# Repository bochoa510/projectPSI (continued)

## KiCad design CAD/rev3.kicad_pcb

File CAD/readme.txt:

Created using OnShape 3D CAD and 3D printed test parts using Makerbot Replicator 5th Gen 

Link to part document
https://cad.onshape.com/documents/6e8889402c3ba4208828449b/w/36755877a1c921f2bab17a01/e/a95ed9e188de5fe185a65eca

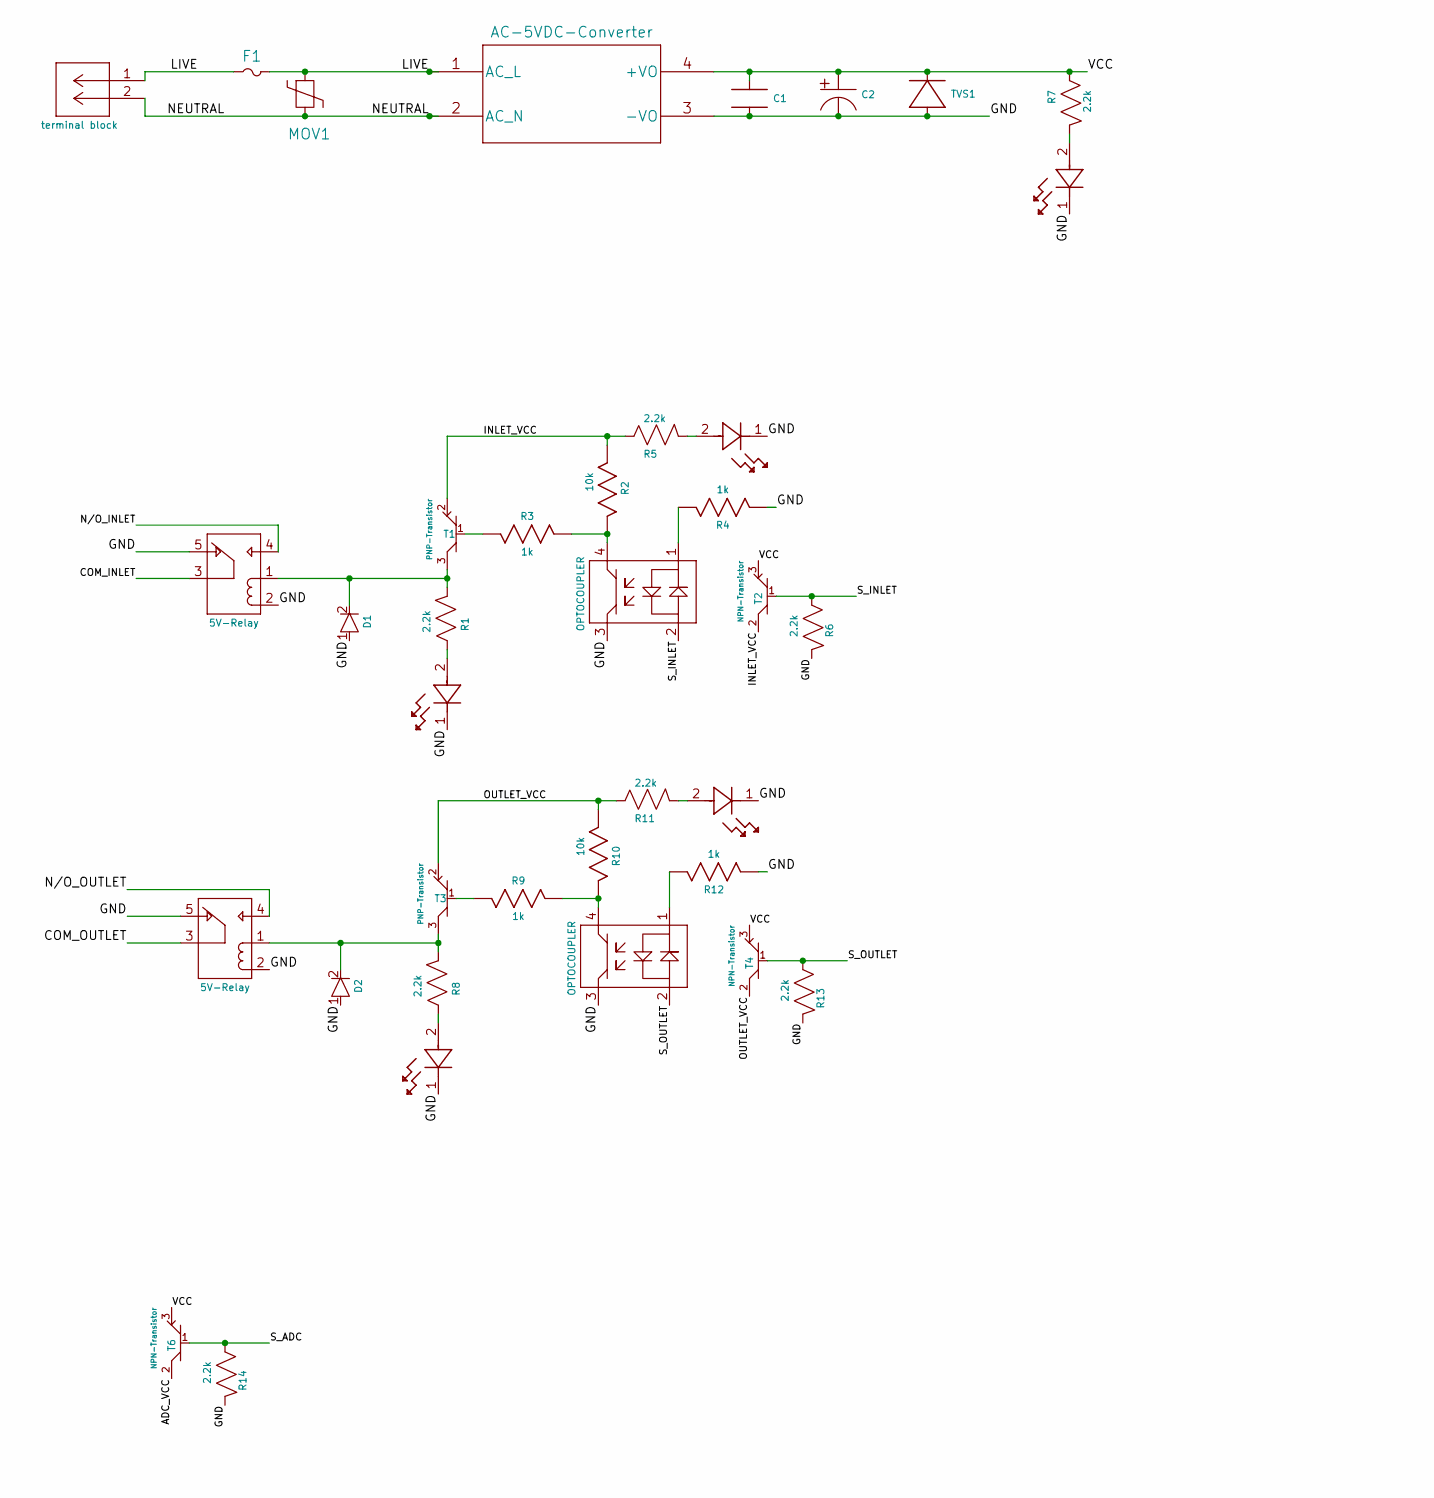
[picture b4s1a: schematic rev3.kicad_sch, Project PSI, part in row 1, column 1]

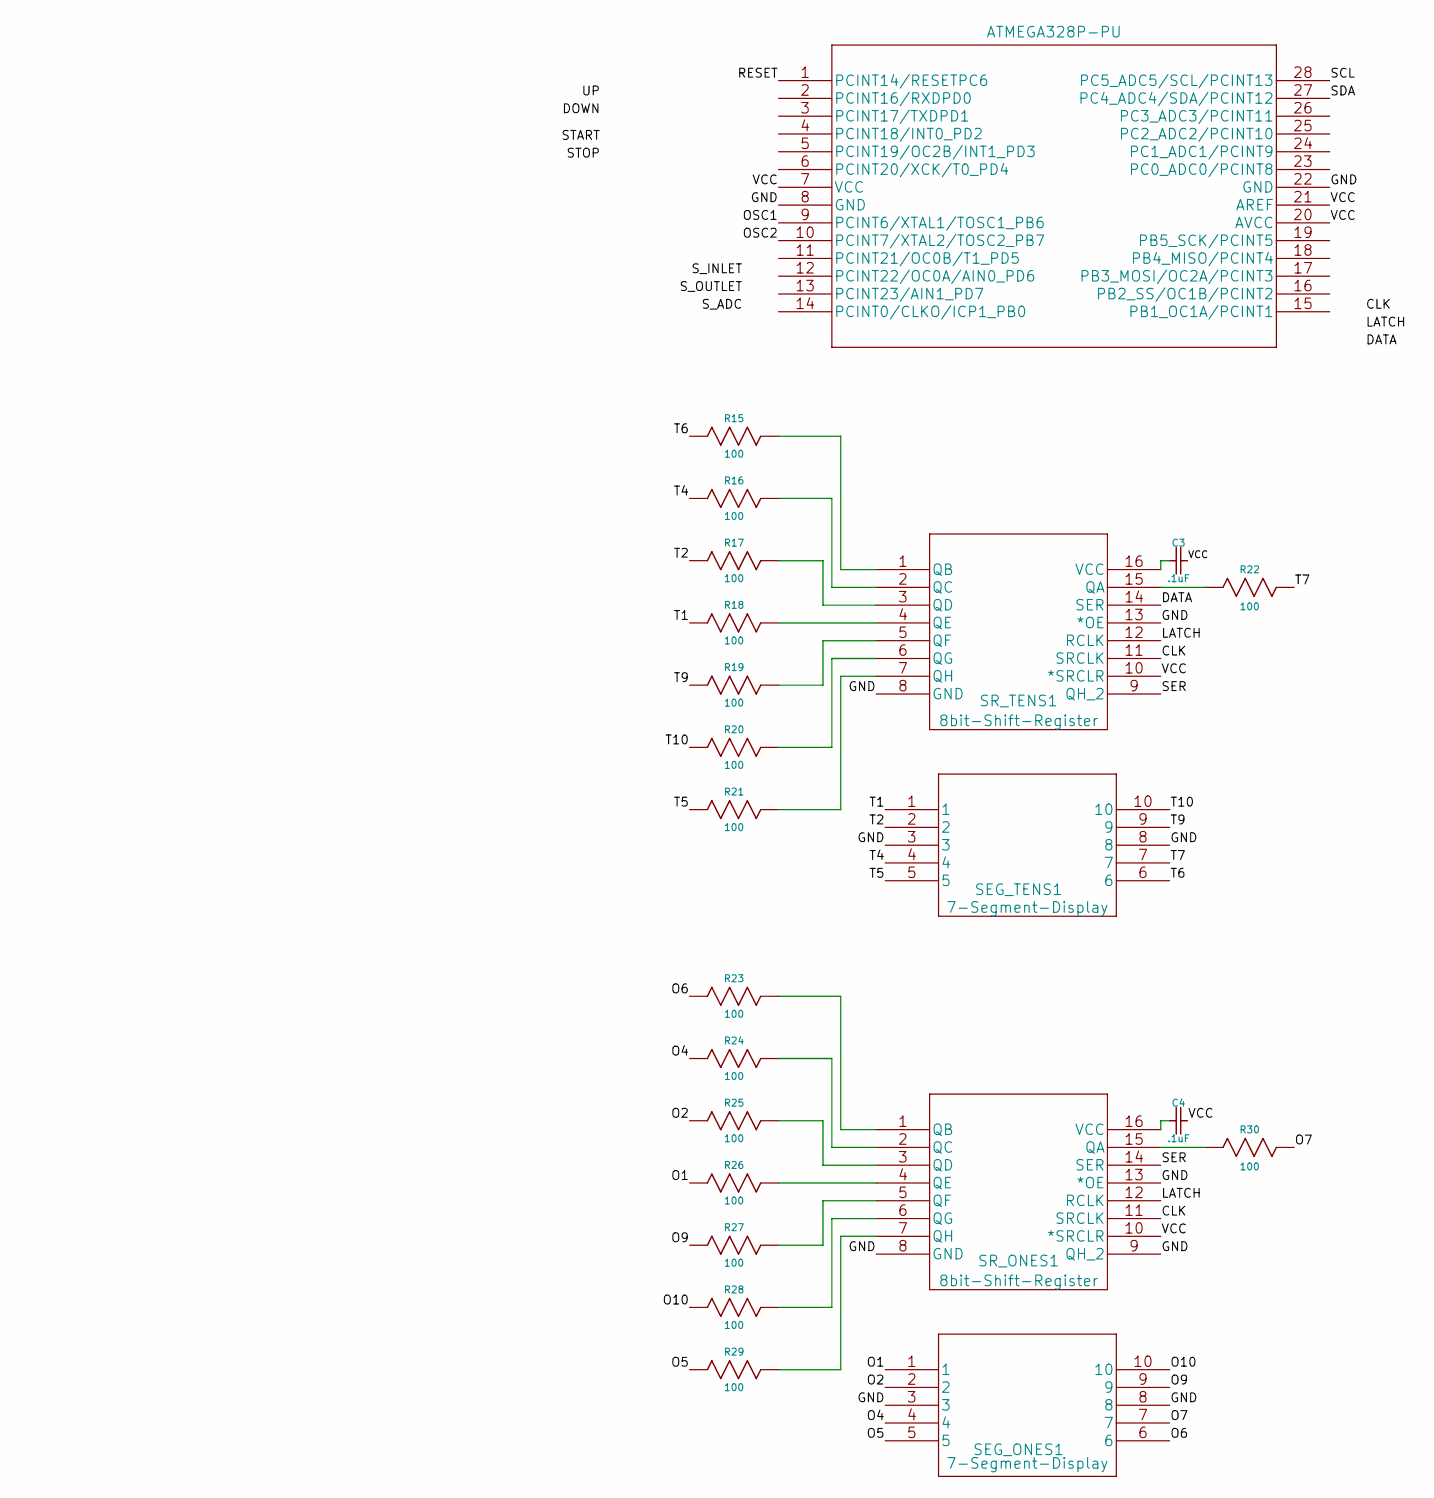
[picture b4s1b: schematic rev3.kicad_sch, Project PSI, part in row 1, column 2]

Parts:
C1: 1uF-Ceramic-Capacitor; 1uF ceramic capacitor
C2: 220uF-Electrolytic-Capacitor; 220uF electrolytic capacitor
C3, C4: .1uF; .1uF ceramic capacitor
D1, D2: Small-Signal-Diode; small signal diode
F1: FUSE
J1, J3: 5V-Relay; 5V Relay
J2: terminal block; 2-pin-terminal-block
LED1, LED3, LED5: green led; green LED
LED2, LED4: red led; red LED
MOV1: 470V-Varistor; 470V Varistor
Q1, Q2: OPTOCOUPLER; optocoupler
R1, R5, R6, R7, R8, R11, R13, R14: 2.2k; 2.2kohm resisitor
R2, R10: 10k; 10kohm resistor
R3, R4, R9, R12: 1k; 1kohm resistor
R15, R16, R17, R18, R19, R20, R21, R22, R23, R24, R25, R26, R27, R28, R29, R30: 100; 100ohm resistor
SEG_ONES1: 7-Segment-Display; 7 segment display
SEG_TENS1: 7-Segment-Display; 7 segment display
SR_ONES1: 8bit-Shift-Register; 8 bit shift register
SR_TENS1: 8bit-Shift-Register; 8 bit shift register
T1, T3: PNP-Transistor; PNP Transistor
T2, T4, T6: NPN-Transistor; NPN Transistor
TVS1: 7A-TVS-DIODE; 7A TVS diode
p1: ATMEGA328P-PU
u1: AC-5VDC-Converter; ac-dc converter

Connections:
/ADC_VCC: T6.2
/COM_INLET: J1.3
/COM_OUTLET: J3.3
/GND: C1.1, C2.2, D1.1, D2.1, J1.2, J1.5, J3.2, J3.5, LED1.1, LED2.1, LED3.1, LED4.1, LED5.1, Q1.3, Q2.3, R4.2, R6.1, R12.2, R13.1, R14.1, SEG_ONES1.3, SEG_ONES1.8, SEG_TENS1.3, SEG_TENS1.8, SR_ONES1.8 (GND), SR_ONES1.9 (QH_2), SR_ONES1.13 (*OE), SR_TENS1.8 (GND), SR_TENS1.13 (*OE), TVS1.2, p1.8 (GND), p1.22 (GND), u1.3 (-VO); also elsewhere on the board
/INLET_VCC: R2.2, R5.2, T1.2, T2.2
/LIVE: F1.1, F1.2, J2.1, MOV1.2, u1.1 (AC_L)
/NEUTRAL: J2.2, MOV1.1, u1.2 (AC_N)
/N/O_INLET: J1.4
/N/O_OUTLET: J3.4
/O1: R26.1, SEG_ONES1.1
/O2: R25.1, SEG_ONES1.2
/O4: R24.1, SEG_ONES1.4
/O5: R29.1, SEG_ONES1.5
/O6: R23.1, SEG_ONES1.6
/O7: R30.1, SEG_ONES1.7
/O9: R27.1, SEG_ONES1.9
/O10: R28.1, SEG_ONES1.10
/OSC1: p1.9 (PCINT6/XTAL1/TOSC1_PB6)
/OSC2: p1.10 (PCINT7/XTAL2/TOSC2_PB7)
/OUTLET_VCC: R10.2, R11.2, T3.2, T4.2
/RESET: p1.1 (PCINT14/RESETPC6)
/SCL: p1.28 (PC5_ADC5/SCL/PCINT13)
/SDA: p1.27 (PC4_ADC4/SDA/PCINT12)
/S_ADC: R14.2, T6.1
/S_INLET: Q1.2, R6.2, T2.1
/S_OUTLET: Q2.2, R13.2, T4.1
/T1: R18.1, SEG_TENS1.1
/T2: R17.1, SEG_TENS1.2
/T4: R16.1, SEG_TENS1.4
/T5: R21.1, SEG_TENS1.5
/T6: R15.1, SEG_TENS1.6
/T7: R22.1, SEG_TENS1.7
/T9: R19.1, SEG_TENS1.9
/T10: R20.1, SEG_TENS1.10
/VCC: C1.2, C2.1, C3.2, C4.2, R7.2, SR_ONES1.10 (*SRCLR), SR_TENS1.10 (*SRCLR), T2.3, T4.3, T6.3, TVS1.1, p1.7 (VCC), p1.20 (AVCC), p1.21 (AREF), u1.4 (+VO); also elsewhere on the board
unnamed: D1.2, J1.1, R1.1, T1.3
unnamed: D2.2, J3.1, R8.1, T3.3
unnamed: LED1.2, R5.1
unnamed: LED2.2, R1.2
unnamed: LED3.2, R7.1
unnamed: LED4.2, R8.2
unnamed: LED5.2, R11.1
unnamed: Q1.1, R4.1
unnamed: Q1.4, R2.1, R3.1
unnamed: Q2.1, R12.1
unnamed: Q2.4, R9.1, R10.1
unnamed: R3.2, T1.1
unnamed: R9.2, T3.1
unnamed: SR_ONES1.11 (SRCLK), SR_TENS1.11 (SRCLK)
unnamed: SR_ONES1.12 (RCLK), SR_TENS1.12 (RCLK)
unnamed: SR_ONES1.14 (SER), SR_TENS1.9 (QH_2)
unnamed 55: R30.2, SR_ONES1.15 (QA); also elsewhere on the board
unnamed 56: R23.2, SR_ONES1.1 (QB); also elsewhere on the board
unnamed 57: R24.2, SR_ONES1.2 (QC); also elsewhere on the board
unnamed 58: R25.2, SR_ONES1.3 (QD); also elsewhere on the board
unnamed 59: R26.2, SR_ONES1.4 (QE); also elsewhere on the board
unnamed 60: R27.2, SR_ONES1.5 (QF); also elsewhere on the board
unnamed 61: R28.2, SR_ONES1.6 (QG); also elsewhere on the board
unnamed 62: R29.2, SR_ONES1.7 (QH); also elsewhere on the board
unnamed 63: C4.1, SR_ONES1.16 (VCC); also elsewhere on the board
unnamed 64: R22.2, SR_TENS1.15 (QA); also elsewhere on the board
unnamed 65: R15.2, SR_TENS1.1 (QB); also elsewhere on the board
unnamed 66: R16.2, SR_TENS1.2 (QC); also elsewhere on the board
unnamed 67: R17.2, SR_TENS1.3 (QD); also elsewhere on the board
unnamed 68: R18.2, SR_TENS1.4 (QE); also elsewhere on the board
unnamed 69: R19.2, SR_TENS1.5 (QF); also elsewhere on the board
unnamed 70: R20.2, SR_TENS1.6 (QG); also elsewhere on the board
unnamed 71: R21.2, SR_TENS1.7 (QH); also elsewhere on the board
unnamed 72: C3.1, SR_TENS1.16 (VCC); also elsewhere on the board

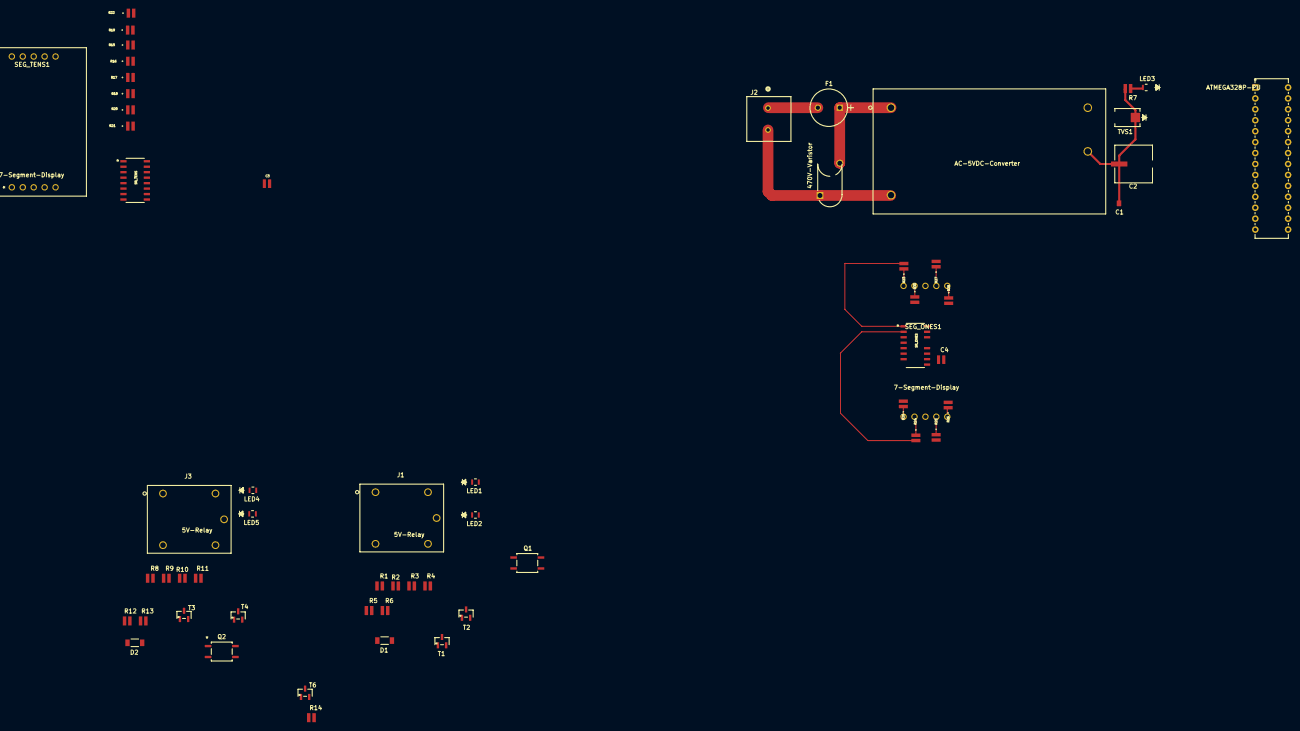
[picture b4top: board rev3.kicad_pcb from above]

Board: 2 copper layers, 60 parts (1 on the bottom side), 59 nets.

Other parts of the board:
SR_ONES: 8bit-Shift-Register; 8 bit shift register
SR_TENS: 8bit-Shift-Register; 8 bit shift register

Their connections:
/CLK: SR_ONES.11 (SRCLK), SR_TENS.11 (SRCLK)
/GND: SR_ONES.8 (GND), SR_ONES.9 (QH_2), SR_ONES.13 (*OE), SR_TENS.8 (GND), SR_TENS.13 (*OE); also elsewhere on the board
/LATCH: SR_ONES.12 (RCLK), SR_TENS.12 (RCLK)
/SER: SR_ONES.14 (SER), SR_TENS.9 (QH_2)
/VCC: SR_ONES.10 (*SRCLR), SR_TENS.10 (*SRCLR); also elsewhere on the board
unnamed 55: SR_ONES.15 (QA); also elsewhere on the board
unnamed 56: SR_ONES.1 (QB); also elsewhere on the board
unnamed 57: SR_ONES.2 (QC); also elsewhere on the board
unnamed 58: SR_ONES.3 (QD); also elsewhere on the board
unnamed 59: SR_ONES.4 (QE); also elsewhere on the board
unnamed 60: SR_ONES.5 (QF); also elsewhere on the board
unnamed 61: SR_ONES.6 (QG); also elsewhere on the board
unnamed 62: SR_ONES.7 (QH); also elsewhere on the board
unnamed 63: SR_ONES.16 (VCC); also elsewhere on the board
unnamed 64: SR_TENS.15 (QA); also elsewhere on the board
unnamed 65: SR_TENS.1 (QB); also elsewhere on the board
unnamed 66: SR_TENS.2 (QC); also elsewhere on the board
unnamed 67: SR_TENS.3 (QD); also elsewhere on the board
unnamed 68: SR_TENS.4 (QE); also elsewhere on the board
unnamed 69: SR_TENS.5 (QF); also elsewhere on the board
unnamed 70: SR_TENS.6 (QG); also elsewhere on the board
unnamed 71: SR_TENS.7 (QH); also elsewhere on the board
unnamed 72: SR_TENS.16 (VCC); also elsewhere on the board

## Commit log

2022-09-29 Add files via upload
    9/28/2022
2022-12-23 Create rev1
2022-12-23 Add files via upload
    moved from main branch into rev1
2022-12-23 Rename mainControl.ino to rev1/maincontrol.ino
2022-12-23 Rename readme.txt to readme
2022-12-23 Rename readme to readme.md
2022-12-23 Rename readme.md to README.md
2022-12-23 rev2 maincontrol
2023-02-28 README
2023-08-10 Typical Connections
2023-08-10 Typical Connections.md
2023-08-10 Module Schematic.md
2023-08-10 example.ino
2023-08-10 README.md
2023-08-11 Moved rev1 and rev2 to Previous versions folder
2024-03-15 Create ADC
2024-05-02 updated schematic, layout and parts library
2024-05-02 updated files
2024-05-24 updated board and kicad lib
2024-05-25 updated kicad board and parts library
2024-05-25 updated board for AC optimization
2024-05-29 more CAD files and updated layout
2024-05-31 updated cad files
